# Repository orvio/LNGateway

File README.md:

# LNGateway
LNGateway is an opto isolated DIY interface between Loconet and a serial interface based on an Arduino micro.

The main purpose is to provide a gateway for throttle messages between wifi trottles connected to JMRI and a DCC command station.
It understands enough Loconet to block certain message types in order to cut down on traffic on either side of the bridge.

Additional documentation and instructions are available under [https://orvio.github.io/LNGateway](https://orvio.github.io/LNGateway)

It can use a i2c OLED display to show the messages passed through it.

It works in JMRI with the LocoBuffer interface driver.

The TX_PIN must be set to 5 if the circuit is built as documented in the KiCad files. It is compatible with the LocoLinx example sketch from the LocoNet library as long as the TX_PIN is set correctly.

The board design matches the mounting hole spacing of a Raspberry Pi.

Full board:

Board without display and Arduino:

Detail view:

Modification to have the V2 circuit on the V1 board:

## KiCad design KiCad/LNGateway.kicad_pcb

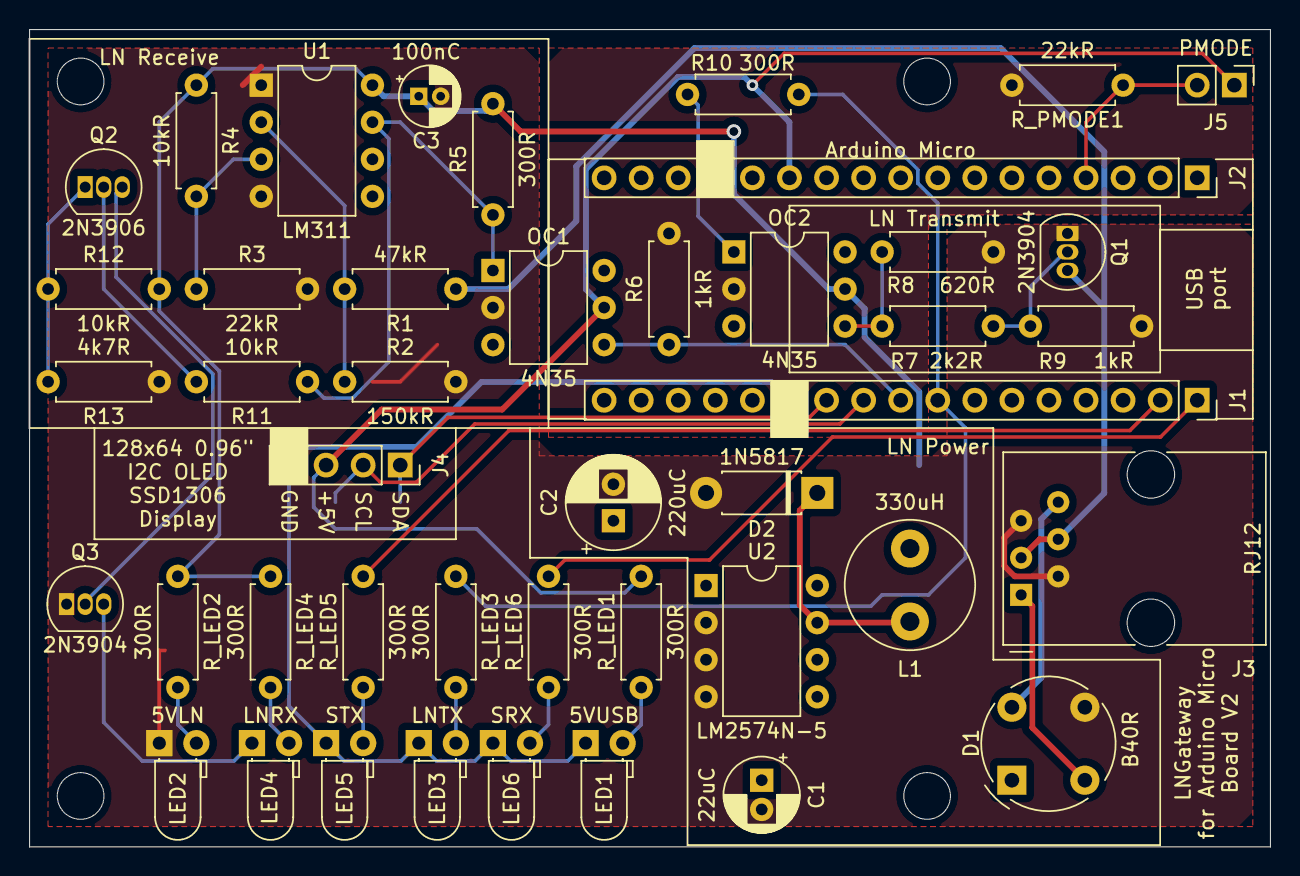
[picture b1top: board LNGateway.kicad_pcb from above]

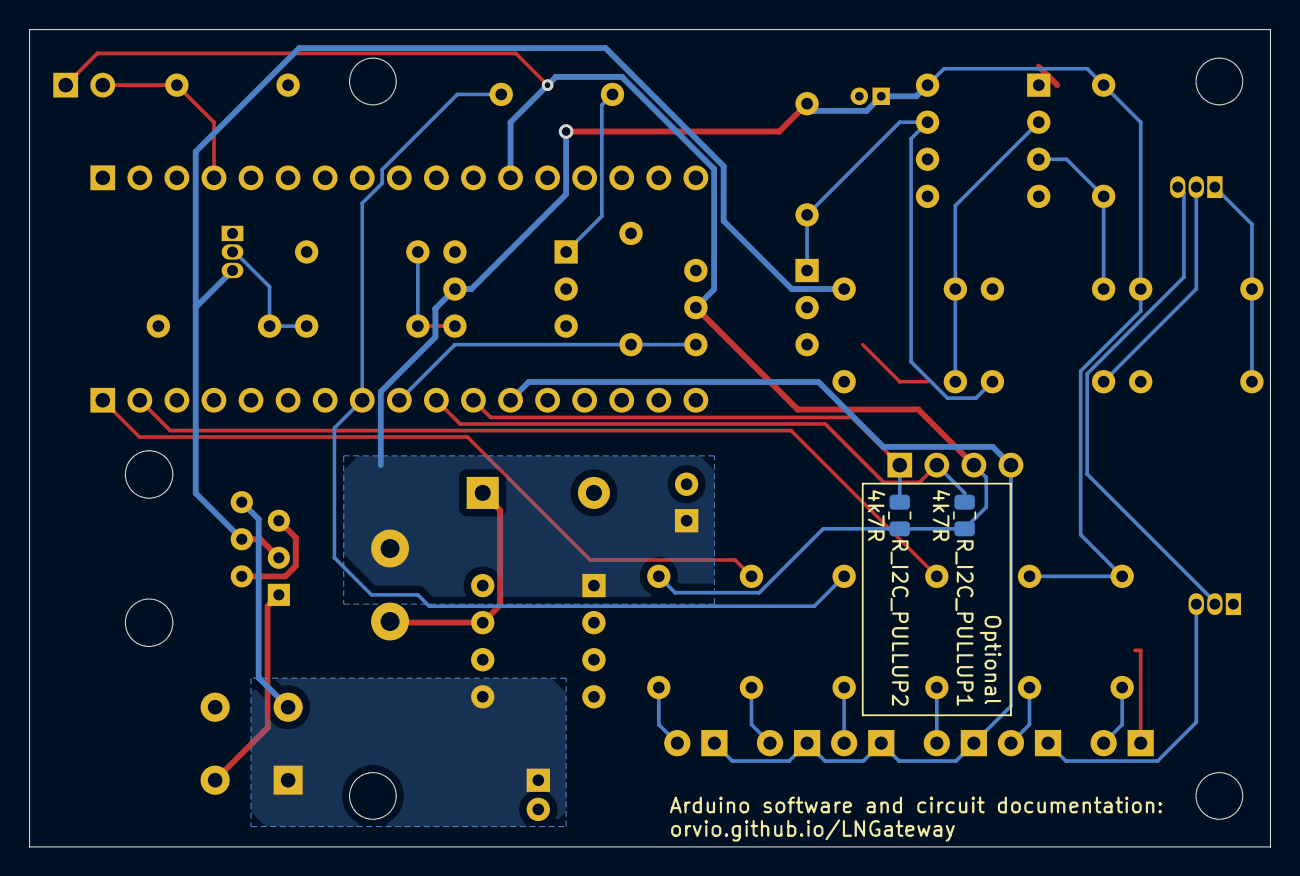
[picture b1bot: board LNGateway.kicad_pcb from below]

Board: 2 copper layers, 85.0 x 56.0 mm, 46 parts (2 on the bottom side), 32 nets.

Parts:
C1: 22uC; CP_Radial_D5.0mm_P2.00mm
C2: 220uC; CP_Radial_D6.3mm_P2.50mm
C3: 100nC; CP_Radial_D4.0mm_P1.50mm
D1: B40R; Diode_Bridge_Round_D9.0mm
D2: 1N5817; D_DO-41_SOD81_P7.62mm_Horizontal
J1, J2: Conn_01x17_Female; PinSocket_1x17_P2.54mm_Vertical
J3: RJ12; RJ12_Amphenol_54601
J4: Conn_01x04_Female; PinSocket_1x04_P2.54mm_Vertical
J5: Conn_01x02_Male; PinHeader_1x02_P2.54mm_Vertical
L1: 330uH; L_Radial_D8.7mm_P5.00mm_Fastron_07HCP
LED1, LED2, LED3, LED4, LED5, LED6: LED; LED_D3.0mm_Horizontal_O1.27mm_Z2.0mm
OC1, OC2: 4N35; DIP-6_W7.62mm
Q1, Q3: 2N3904; TO-92_Inline
Q2: 2N3906; TO-92_Inline
R1: 47kR; R_Axial_DIN0207_L6.3mm_D2.5mm_P7.62mm_Horizontal
R2: 150kR; R_Axial_DIN0207_L6.3mm_D2.5mm_P7.62mm_Horizontal
R3: 22kR; R_Axial_DIN0207_L6.3mm_D2.5mm_P7.62mm_Horizontal
R4, R11, R12: 10kR; R_Axial_DIN0207_L6.3mm_D2.5mm_P7.62mm_Horizontal
R5, R10: 300R; R_Axial_DIN0207_L6.3mm_D2.5mm_P7.62mm_Horizontal
R6, R9: 1kR; R_Axial_DIN0207_L6.3mm_D2.5mm_P7.62mm_Horizontal
R7: 2k2R; R_Axial_DIN0207_L6.3mm_D2.5mm_P7.62mm_Horizontal
R8: 620R; R_Axial_DIN0207_L6.3mm_D2.5mm_P7.62mm_Horizontal
R13: 4k7R; R_Axial_DIN0207_L6.3mm_D2.5mm_P7.62mm_Horizontal
R_I2C_PULLUP1, R_I2C_PULLUP2: 4k7R; R_0805_2012Metric
R_LED1, R_LED2, R_LED3, R_LED4, R_LED5, R_LED6: 300R; R_Axial_DIN0207_L6.3mm_D2.5mm_P7.62mm_Horizontal
R_PMODE1: 22kR; R_Axial_DIN0207_L6.3mm_D2.5mm_P7.62mm_Horizontal
U1: LM311; DIP-8_W7.62mm
U2: LM2574N-5; DIP-8_W7.62mm

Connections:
+5V: J2.12, J4.3, J5.1, OC1.5, R_I2C_PULLUP1.2, R_I2C_PULLUP2.2, R_LED1.2
/1V5: Q2.1, R12.1, R13.2
/LN: J3.3, J3.4, Q1.3, R1.1
/LN_5V_RAW: D2.1, L1.2, U2.7
/LN_RX: OC1.1, R5.1, R11.1, U1.7
/LN_RX_Arduino: J1.9, OC1.4, R6.1
/LN_TX: OC2.4, R7.1, R8.1
/LN_TX_1V5: Q1.2, R7.2, R9.1
/LN_TX_Arduino: J1.8, R10.1, R_LED3.1
/LN_VIN: C1.1, D1.1, U2.5
/PMODE: J2.4, J5.2, R_PMODE1.1
/RAIl_SYNC_1: D1.4, J3.6
/RAIl_SYNC_2: D1.2, J3.1
/REF_3V44: R3.1, R4.2, U1.3
/SCL: J1.10, J4.2, R_I2C_PULLUP1.1
/SDA: J1.11, J4.1, R_I2C_PULLUP2.1
/SERIAL_RX: J1.1, R_LED6.2
/SERIAL_TX: J1.2, R_LED5.2
/VLN_IN_9NOM_3V8MIN_18VMAX: R1.2, R2.1, U1.2
GND1: C1.2, C2.2, C3.2, D1.3, D2.2, J3.2, J3.5, LED2.1, OC1.2, Q1.1, Q3.1, R2.2, R3.2, R8.2, R9.2, R13.1, U1.1, U1.4, U2.2, U2.3, U2.4
GND2: J1.12, J2.14, J4.4, LED1.1, LED3.1, LED5.1, LED6.1, OC2.2, R6.2, R_PMODE1.2
unnamed: LED1.2, R_LED1.1
unnamed: LED2.2, R_LED2.2
unnamed: LED3.2, R_LED3.2
unnamed: LED4.1, Q3.3
unnamed: LED4.2, R_LED4.2
unnamed: LED5.2, R_LED5.1
unnamed: LED6.2, R_LED6.1
unnamed: OC2.1, R10.2
unnamed: Q2.2, R11.2
unnamed: Q2.3, Q3.2
VDD: C2.1, C3.1, L1.1, OC2.5, R4.1, R5.2, R12.2, R_LED2.1, R_LED4.1, U1.8, U2.1

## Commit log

2021-11-14 moved sketch to correct folder
2021-11-14 Fixed typo
2021-11-14 Added V1 of circuit and board design. It does not work properly like this, so please don't actually use it.
2021-11-14 Updated circuit and board design to improve LN TX reliability
2021-11-14 Generated BOM files
2021-11-14 Added shopping list
2021-11-16 Renamed everything to LNGateway to avoid naming conflict with the existing LocoBridge BT interface
2021-11-16 Updated board silk screen for new name
2021-11-16 Updated sketch and REAMDE with new name
2021-11-17 Set theme jekyll-theme-slate
2021-11-17 Added Images
2021-11-18 Added schematic pdf
2021-11-18 added scaled down versions of the photos
2021-12-09 Added programming instructions
2021-12-09 Added link to programming instructions
2021-12-09 Fixed typos
2021-12-14 Added link to pages
2021-12-20 Added title to schematic
2021-12-20 Added reference to github repo
2022-02-13 Updated parts list
2022-02-19 No longer blocking throttle messages from LN bus
    Blocking throttle messages from LN seems to sometimes confuse JMRI
